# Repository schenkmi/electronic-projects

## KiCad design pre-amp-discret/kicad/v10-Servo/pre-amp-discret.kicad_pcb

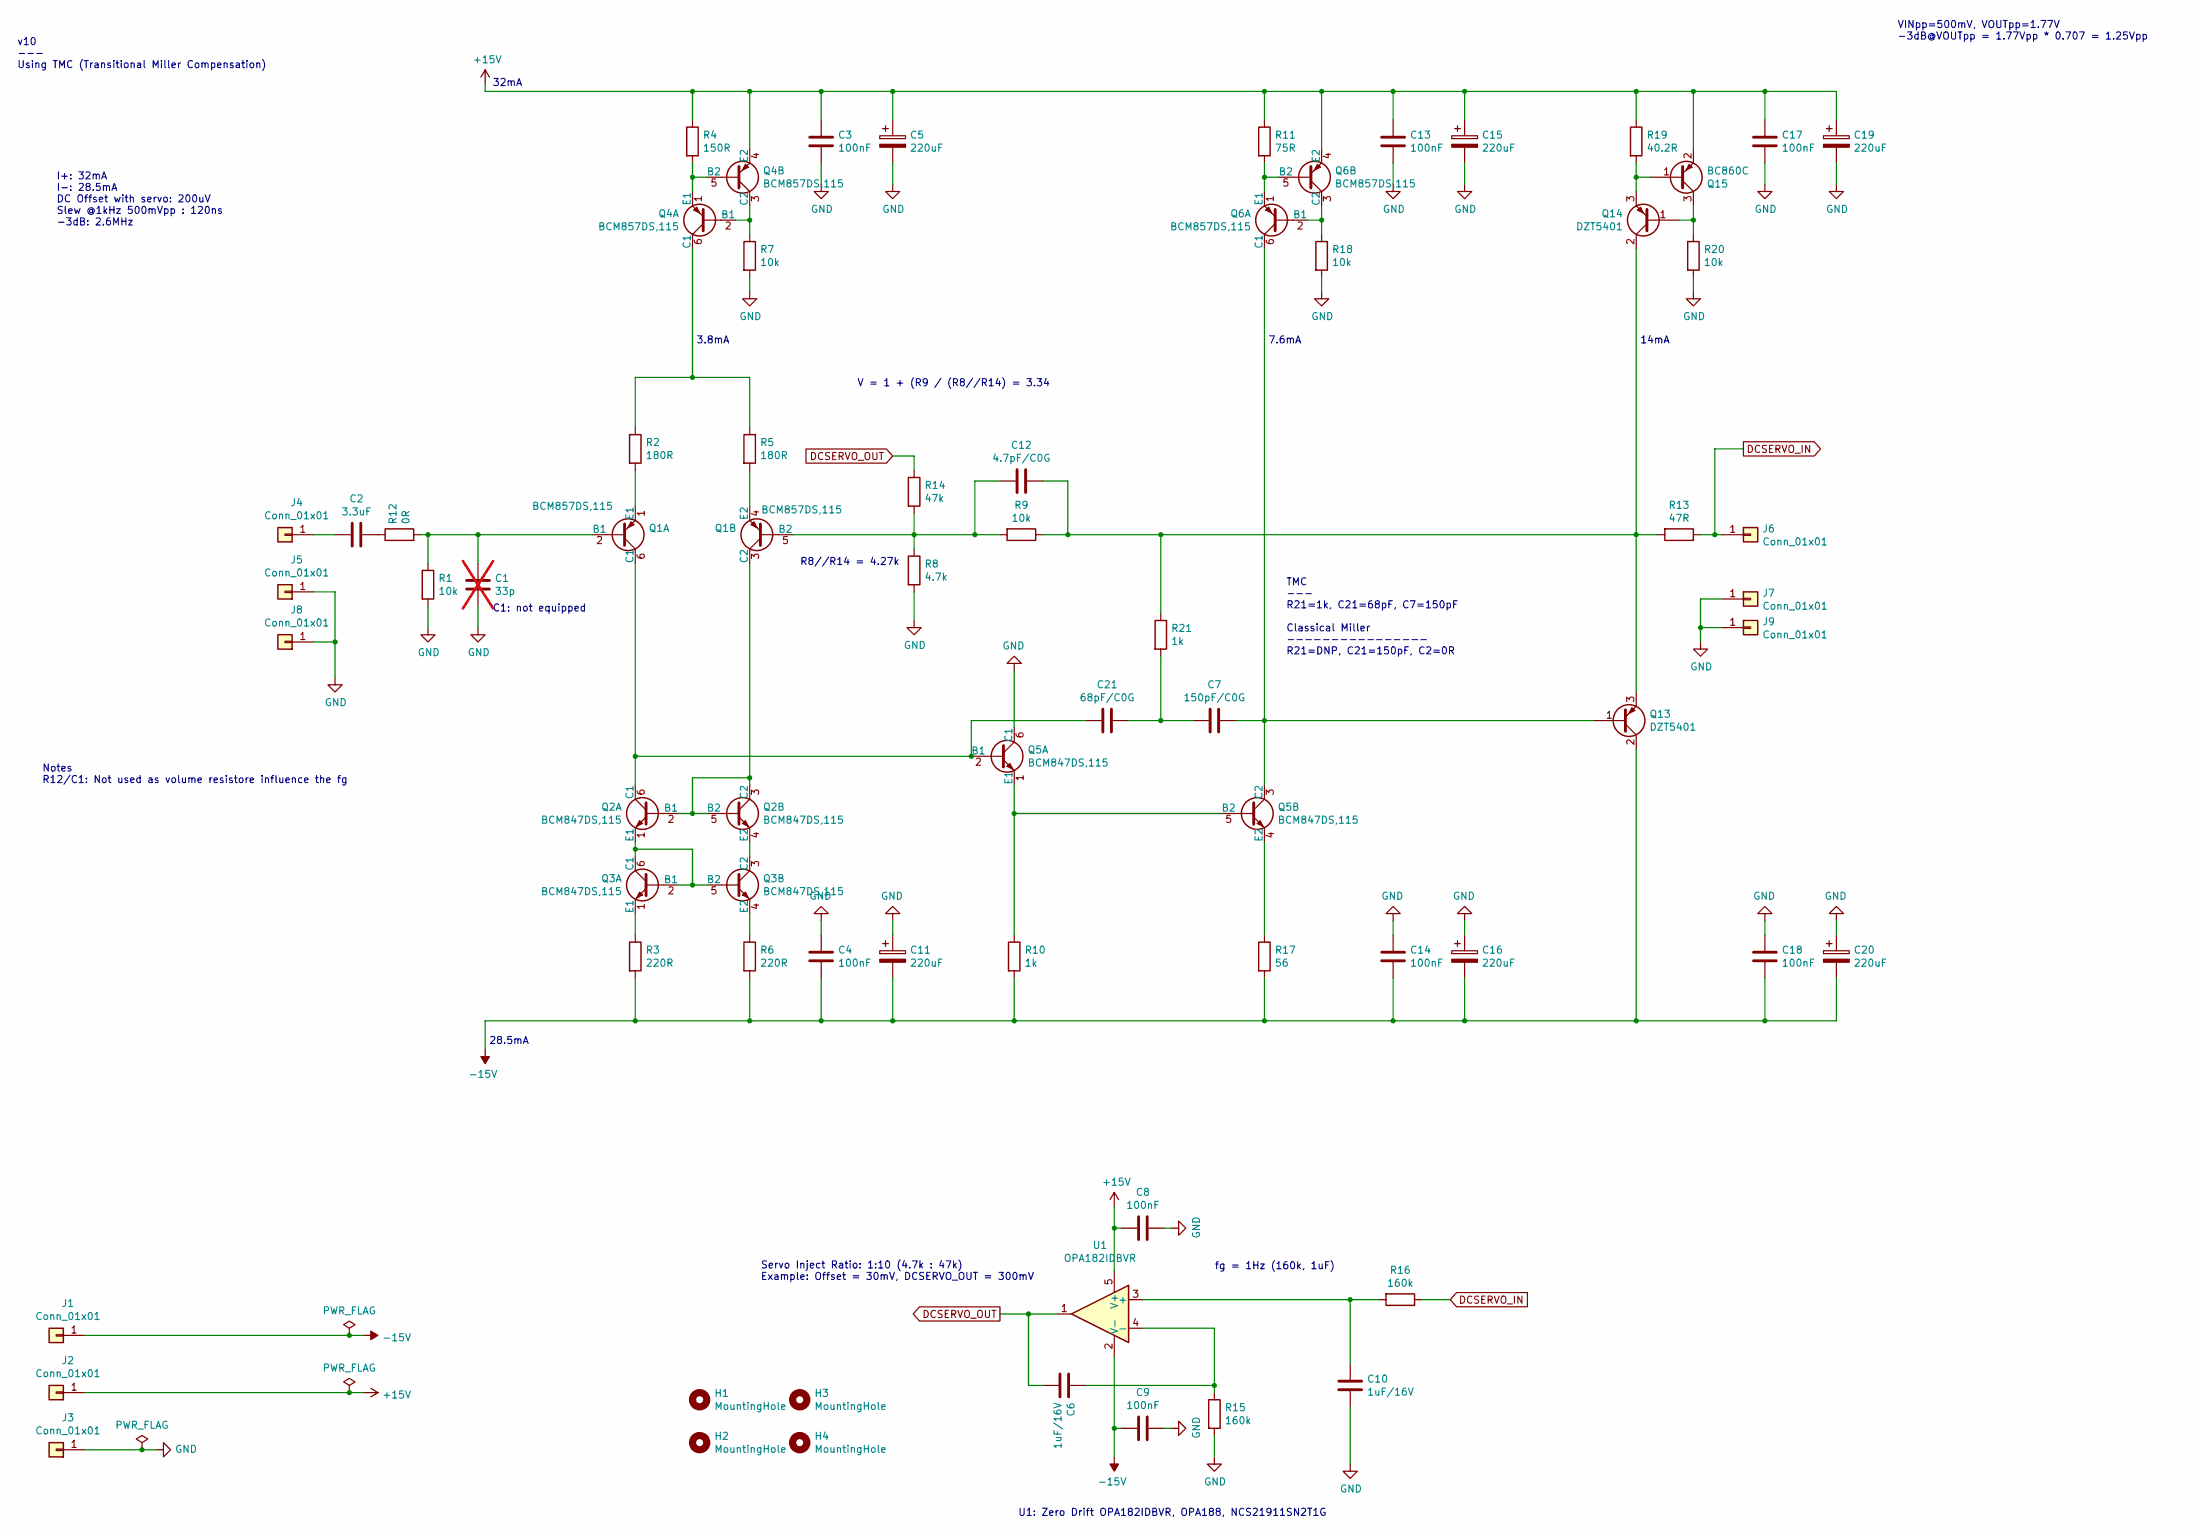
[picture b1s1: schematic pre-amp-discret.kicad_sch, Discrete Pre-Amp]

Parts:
C1: 33p; C_0805_2012Metric_Pad1.18x1.45mm_HandSolder; not fitted
C2: 3.3uF; C_Rect_L7.2mm_W7.2mm_P5.00mm_FKS2_FKP2_MKS2_MKP2
C3, C4, C13, C14, C17, C18: 100nF; C_1210_3225Metric_Pad1.33x2.70mm_HandSolder
C5, C11, C15, C16, C19, C20: 220uF; CP_Radial_D8.0mm_P3.50mm
C6, C10: 1uF/16V; C_1210_3225Metric_Pad1.33x2.70mm_HandSolder
C7: 150pF/C0G; C_0805_2012Metric_Pad1.18x1.45mm_HandSolder
C8, C9: 100nF; C_0603_1608Metric_Pad1.08x0.95mm_HandSolder
C12: 4.7pF/C0G; C_0805_2012Metric_Pad1.18x1.45mm_HandSolder
C21: 68pF/C0G; C_0805_2012Metric_Pad1.18x1.45mm_HandSolder
H1, H2, H3, H4: MountingHole; MountingHole_3.2mm_M3
J1, J2, J3, J4, J5, J6, J7, J8, J9: Conn_01x01; Pin_D1.0mm_L10.0mm
Q1, Q4, Q6: BCM857DS,115; SC-74-6_1.5x2.9mm_P0.95mm
Q2, Q3, Q5: BCM847DS,115; SC-74-6_1.5x2.9mm_P0.95mm
Q13, Q14: DZT5401; SOT-223-3_TabPin2
Q15: BC860C; SOT-23
R1, R7, R9, R18, R20: 10k; R_0805_2012Metric_Pad1.20x1.40mm_HandSolder
R2, R5: 180R; R_0805_2012Metric_Pad1.20x1.40mm_HandSolder
R3, R6: 220R; R_0805_2012Metric_Pad1.20x1.40mm_HandSolder
R4: 150R; R_0805_2012Metric_Pad1.20x1.40mm_HandSolder
R8: 4.7k; R_0805_2012Metric_Pad1.20x1.40mm_HandSolder
R10, R21: 1k; R_0805_2012Metric_Pad1.20x1.40mm_HandSolder
R11: 75R; R_0805_2012Metric_Pad1.20x1.40mm_HandSolder
R12: 0R; R_0805_2012Metric_Pad1.20x1.40mm_HandSolder
R13: 47R; R_0805_2012Metric_Pad1.20x1.40mm_HandSolder
R14: 47k; R_0805_2012Metric_Pad1.20x1.40mm_HandSolder
R15, R16: 160k; R_0805_2012Metric_Pad1.20x1.40mm_HandSolder
R17: 56; R_0805_2012Metric_Pad1.20x1.40mm_HandSolder
R19: 40.2R; R_0805_2012Metric_Pad1.20x1.40mm_HandSolder
U1: OPA182IDBVR; TSOT-23-5

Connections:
+15V: C3.2, C5.1, C8.2, C13.2, C15.1, C17.2, C19.1, J2.1, Q4.4 (E2), Q6.4 (E2), Q15.2 (E), R4.1, R11.1, R19.1, U1.5 (V+)
-15V: C4.1, C9.2, C11.2, C14.1, C16.2, C18.1, C20.2, J1.1, Q13.2 (C), R3.2, R6.2, R10.2, R17.2, U1.2 (V-)
DCSERVO_IN: J6.1, R13.1, R16.1
DCSERVO_OUT: C6.1, R14.1, U1.1
GND: C1.1, C3.1, C4.2, C5.2, C8.1, C9.1, C10.1, C11.1, C13.1, C14.2, C15.2, C16.1, C17.1, C18.2, C19.2, C20.1, J3.1, J5.1, J7.1, J8.1, J9.1, Q5.6 (C1), R1.2, R7.2, R8.2, R15.2, R18.2, R20.2
unnamed: C2.1, R12.1
unnamed: C7.2, C21.1, R21.2
unnamed: C2.2, J4.1
unnamed: C1.2, Q1.2 (B1), R1.1, R12.2
unnamed: C21.2, Q1.6 (C1), Q2.6 (C1), Q5.2 (B1)
unnamed: Q1.1 (E1), R2.2
unnamed: C12.2, Q1.5 (B2), R8.1, R9.2, R14.2
unnamed: Q1.3 (C2), Q2.2 (B1), Q2.3 (C2), Q2.5 (B2)
unnamed: Q1.4 (E2), R5.2
unnamed: Q2.1 (E1), Q3.2 (B1), Q3.5 (B2), Q3.6 (C1)
unnamed: Q2.4 (E2), Q3.3 (C2)
unnamed: Q3.1 (E1), R3.1
unnamed: Q3.4 (E2), R6.1
unnamed: Q4.2 (B1), Q4.3 (C2), R7.1
unnamed: Q4.6 (C1), R2.1, R5.1
unnamed: Q4.1 (E1), Q4.5 (B2), R4.2
unnamed: Q5.1 (E1), Q5.5 (B2), R10.1
unnamed: Q5.4 (E2), R17.1
unnamed: Q6.2 (B1), Q6.3 (C2), R18.1
unnamed: Q6.1 (E1), Q6.5 (B2), R11.2
unnamed: C7.1, Q5.3 (C2), Q6.6 (C1), Q13.1 (B)
unnamed: C12.1, Q13.3 (E), Q14.2 (C), R9.1, R13.2, R21.1
unnamed: Q14.1 (B), Q15.3 (C), R20.1
unnamed: Q14.3 (E), Q15.1 (B), R19.2
unnamed: C10.2, R16.2, U1.3 (+)
unnamed: C6.2, R15.1, U1.4 (-)

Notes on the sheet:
V = 1 + (R9 / (R8//R14) = 3.34
U1: Zero Drift OPA182IDBVR, OPA188, NCS21911SN2T1G
I+: 32mA I-: 28.5mA DC Offset with servo: 200uV Slew @1kHz 500mVpp : 120ns -3dB: 2.6MHz
32mA
R8//R14 = 4.27k
TMC --- R21=1k, C21=68pF, C7=150pF Classical Miller ---------------- R21=DNP, C21=150pF, C2=0R
C1: not equipped
3.8mA
Servo Inject Ratio: 1:10 (4.7k : 47k) Example: Offset = 30mV, DCSERVO_OUT = 300mV
14mA
v10 --- Using TMC (Transitional Miller Compensation)
28.5mA
Notes R12/C1: Not used as volume resistore influence the fg
fg = 1Hz (160k, 1uF)
VINpp=500mV, VOUTpp=1.77V -3dB@VOUTpp = 1.77Vpp * 0.707 = 1.25Vpp
7.6mA

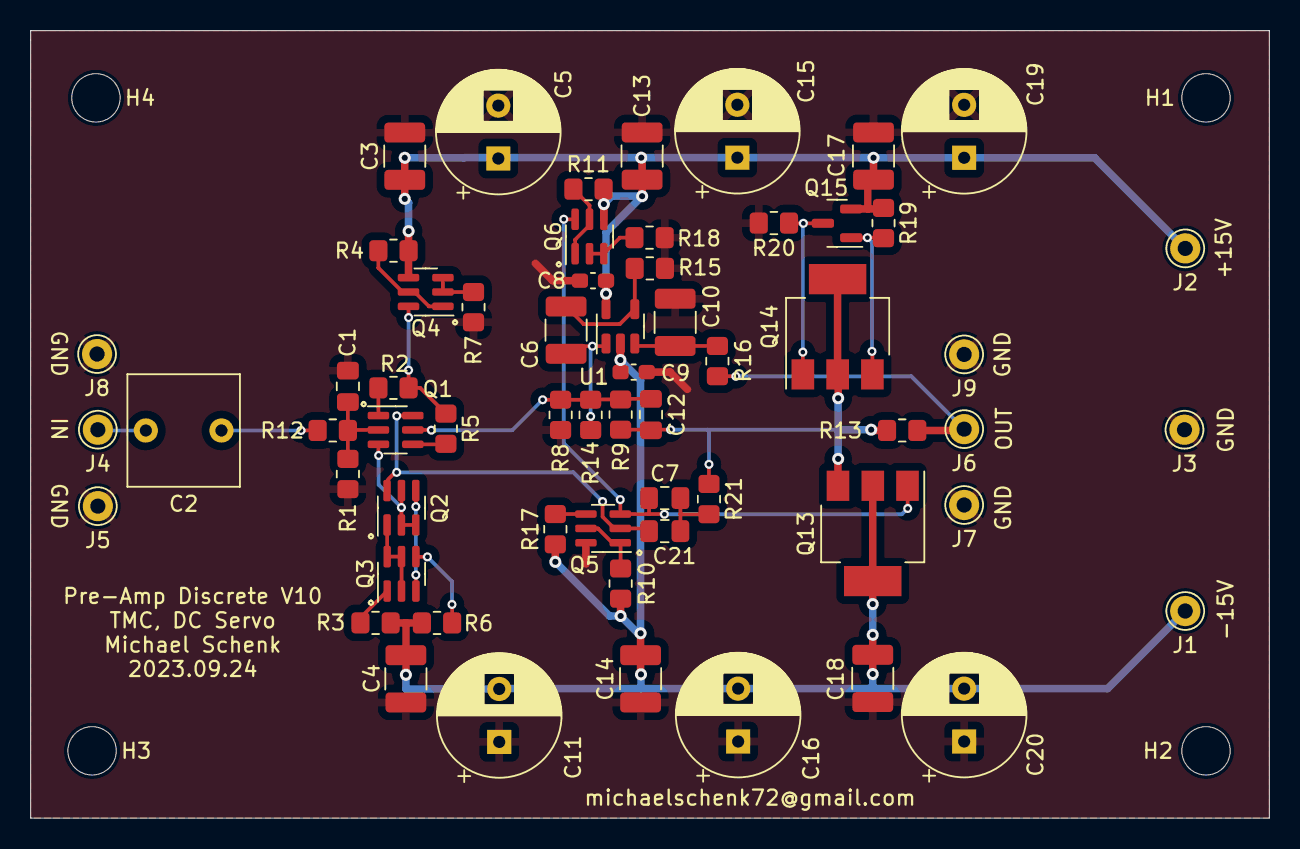
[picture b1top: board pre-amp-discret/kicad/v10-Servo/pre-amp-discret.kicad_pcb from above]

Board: 2 copper layers, 81.9 x 52.1 mm, 65 parts (0 on the bottom side), 31 nets.

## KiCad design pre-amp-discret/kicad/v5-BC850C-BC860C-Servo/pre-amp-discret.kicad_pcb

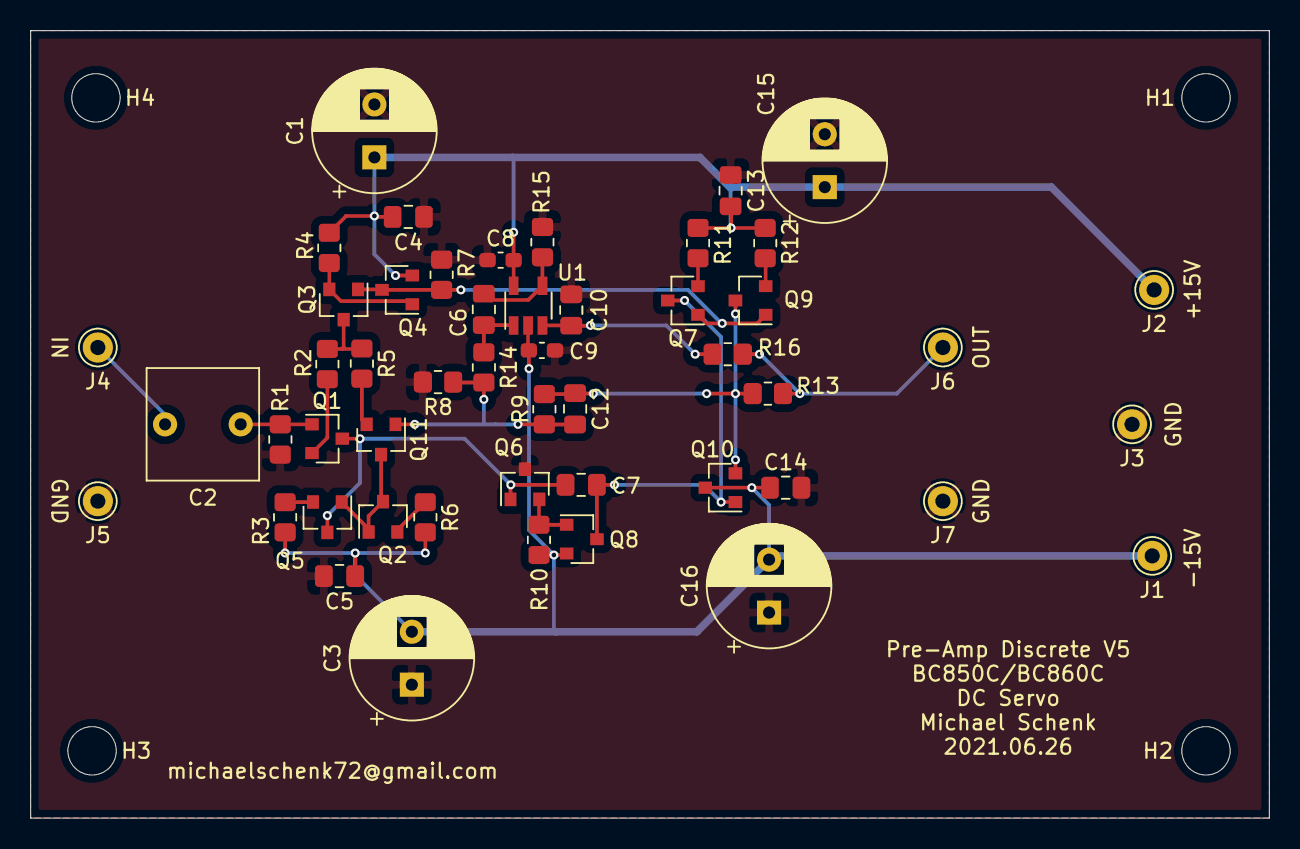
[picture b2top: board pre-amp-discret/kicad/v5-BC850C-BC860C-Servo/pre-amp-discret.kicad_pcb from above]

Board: 2 copper layers, 81.9 x 52.1 mm, 54 parts (0 on the bottom side), 24 nets.

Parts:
C1, C3, C15, C16: 220uF; CP_Radial_D8.0mm_P3.50mm
C2: 2.2uF; C_Rect_L7.2mm_W7.2mm_P5.00mm_FKS2_FKP2_MKS2_MKP2
C4, C5, C13, C14: 100nF; C_0805_2012Metric_Pad1.18x1.45mm_HandSolder
C6, C10: 1uF; C_0805_2012Metric_Pad1.18x1.45mm_HandSolder
C7: 270pF; C_0805_2012Metric_Pad1.18x1.45mm_HandSolder
C8, C9: 100nF; C_0603_1608Metric_Pad1.08x0.95mm_HandSolder
C12: 4.7pF; C_0805_2012Metric_Pad1.18x1.45mm_HandSolder
H1, H2, H3, H4: MountingHole; MountingHole_3.2mm_M3
J1, J2, J3, J4, J5, J6, J7: Conn_01x01; Pin_D1.0mm_L10.0mm
Q1, Q3, Q4, Q7, Q9, Q10, Q11: BC860C; SOT-23
Q2, Q5, Q6, Q8: BC850C; SOT-23
R1, R7, R8, R9, R14: 10k; R_0805_2012Metric_Pad1.20x1.40mm_HandSolder
R2, R5, R11, R12: 100R; R_0805_2012Metric_Pad1.20x1.40mm_HandSolder
R3, R6: 68; R_0805_2012Metric_Pad1.20x1.40mm_HandSolder
R4: 150R; R_0805_2012Metric_Pad1.20x1.40mm_HandSolder
R10: 2k2; R_0805_2012Metric_Pad1.20x1.40mm_HandSolder
R13: 47R; R_0805_2012Metric_Pad1.20x1.40mm_HandSolder
R15, R16: 100k; R_0805_2012Metric_Pad1.20x1.40mm_HandSolder
U1: OPA188xxDBV; TSOT-23-5

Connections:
+15V: C1.1, C4.2, C8.2, C13.2, C15.1, J2.1, Q4.2, R4.1, R11.1, R12.1, U1.5
-15V: C3.2, C5.1, C9.2, C14.1, C16.2, J1.1, Q8.2, Q10.3, R3.2, R6.2, R10.2, U1.2
DCSERVO_IN: J6.1, R13.1, R16.1
DCSERVO_OUT: C6.1, R14.1, U1.1
GND: C1.2, C3.1, C4.1, C5.2, C8.1, C9.1, C10.1, C13.1, C14.2, C15.2, C16.1, J3.1, J5.1, J7.1, Q6.3, R1.2, R7.2, R8.2, R15.2
unnamed: C2.1, Q1.1, R1.1
unnamed: C2.2, J4.1
unnamed: C6.2, R15.1, U1.4
unnamed: C7.1, Q7.3, Q8.3, Q10.1
unnamed: C7.2, Q1.3, Q2.3, Q6.1
unnamed: C10.2, R16.2, U1.3
unnamed: C12.1, Q9.3, Q10.2, R9.1, R13.2
unnamed: C12.2, Q11.1, R8.1, R9.2, R14.2
unnamed: Q1.2, R2.2
unnamed: Q2.2, R3.1
unnamed: Q3.1, Q4.3, Q7.1, Q9.1, R7.1
unnamed: Q3.2, Q4.1, R4.2
unnamed: Q3.3, R2.1, R5.1
unnamed: Q5.2, R6.1
unnamed: Q6.2, Q8.1, R10.1
unnamed: Q7.2, R11.2
unnamed: Q9.2, R12.2
unnamed: Q11.2, R5.2
unnamed: Q2.1, Q5.1, Q5.3, Q11.3
